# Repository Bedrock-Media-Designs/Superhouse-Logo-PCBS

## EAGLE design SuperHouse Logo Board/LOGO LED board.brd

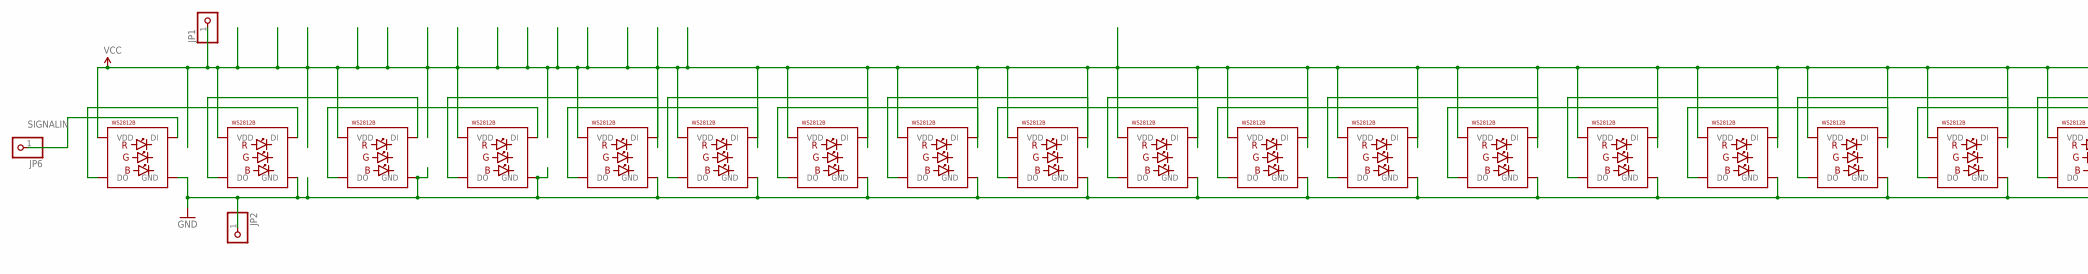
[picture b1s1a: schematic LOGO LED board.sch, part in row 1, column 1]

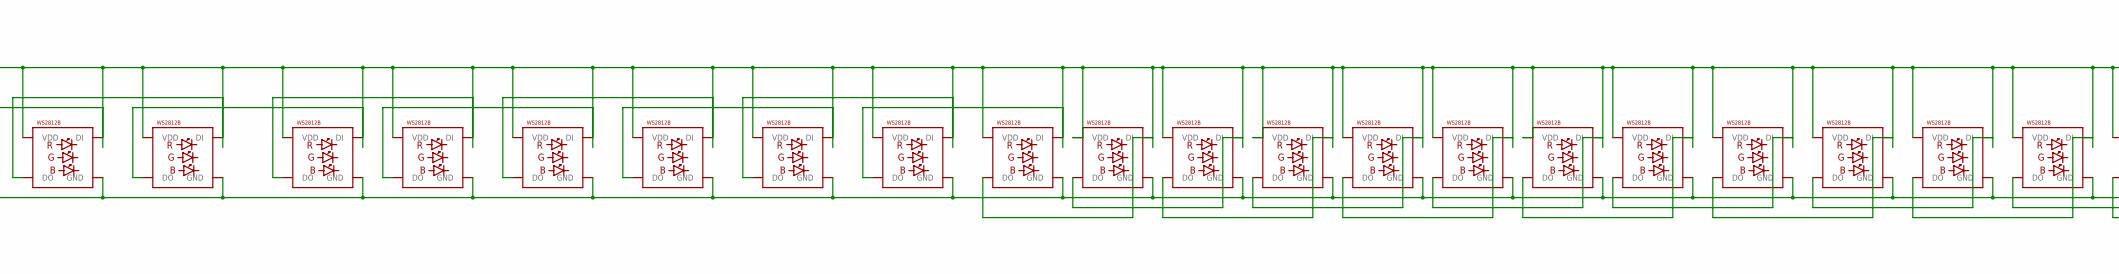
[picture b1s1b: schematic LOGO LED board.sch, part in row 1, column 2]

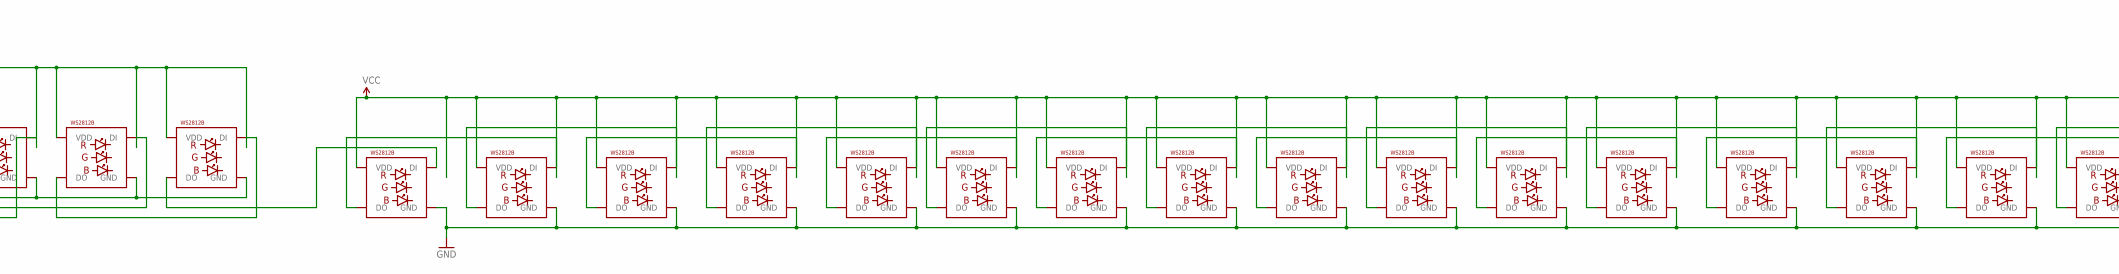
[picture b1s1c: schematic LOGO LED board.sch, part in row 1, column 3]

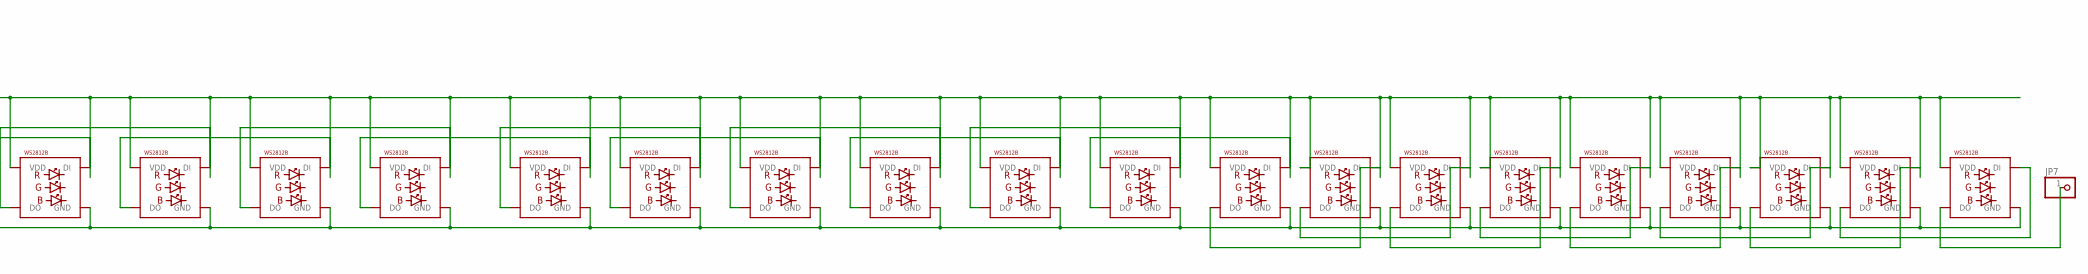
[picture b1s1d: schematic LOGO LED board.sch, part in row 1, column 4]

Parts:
JP1, JP2, JP6, JP7: PINHD-1X1; 1X01
LED1, LED2, LED3, LED4, LED5, LED6, LED7, LED8, LED9, LED10, LED11, LED12, LED13, LED14, LED15, LED16, LED17, LED18, LED19, LED20, LED21, LED22, LED23, LED24, LED25, LED26, LED27, LED28, LED29, LED30, LED31, LED32, LED33, LED34, LED35, LED36, LED37, LED38, LED39, LED40, LED41, LED42, LED43, LED44, LED45, LED46, LED47, LED48, LED49, LED50, LED51, LED52, LED53, LED54, LED55, LED56, LED57, LED58, LED59, LED60, LED61, LED62, LED63, LED64, LED65, LED66, LED67, LED68, LED69, LED70, LED71, LED72, LED73: WS2812B5050; WS2812B

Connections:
5V: JP1.1, LED1.1-VDD (VDD), LED2.1-VDD (VDD), LED3.1-VDD (VDD), LED4.1-VDD (VDD), LED5.1-VDD (VDD), LED6.1-VDD (VDD), LED7.1-VDD (VDD), LED8.1-VDD (VDD), LED9.1-VDD (VDD), LED10.1-VDD (VDD), LED11.1-VDD (VDD), LED12.1-VDD (VDD), LED13.1-VDD (VDD), LED14.1-VDD (VDD), LED15.1-VDD (VDD), LED16.1-VDD (VDD), LED17.1-VDD (VDD), LED18.1-VDD (VDD), LED19.1-VDD (VDD), LED20.1-VDD (VDD), LED21.1-VDD (VDD), LED22.1-VDD (VDD), LED23.1-VDD (VDD), LED24.1-VDD (VDD), LED25.1-VDD (VDD), LED26.1-VDD (VDD), LED27.1-VDD (VDD), LED28.1-VDD (VDD), LED29.1-VDD (VDD), LED30.1-VDD (VDD), LED31.1-VDD (VDD), LED32.1-VDD (VDD), LED33.1-VDD (VDD), LED34.1-VDD (VDD), LED35.1-VDD (VDD), LED36.1-VDD (VDD), LED37.1-VDD (VDD), LED38.1-VDD (VDD), LED39.1-VDD (VDD), LED40.1-VDD (VDD), LED41.1-VDD (VDD), LED42.1-VDD (VDD), LED43.1-VDD (VDD), LED44.1-VDD (VDD), LED45.1-VDD (VDD), LED46.1-VDD (VDD), LED47.1-VDD (VDD), LED48.1-VDD (VDD), LED49.1-VDD (VDD), LED50.1-VDD (VDD), LED51.1-VDD (VDD), LED52.1-VDD (VDD), LED53.1-VDD (VDD), LED54.1-VDD (VDD), LED55.1-VDD (VDD), LED56.1-VDD (VDD), LED57.1-VDD (VDD), LED58.1-VDD (VDD), LED59.1-VDD (VDD), LED60.1-VDD (VDD), LED61.1-VDD (VDD), LED62.1-VDD (VDD), LED63.1-VDD (VDD), LED64.1-VDD (VDD), LED65.1-VDD (VDD), LED66.1-VDD (VDD), LED67.1-VDD (VDD), LED68.1-VDD (VDD), LED69.1-VDD (VDD), LED70.1-VDD (VDD), LED71.1-VDD (VDD), LED72.1-VDD (VDD), LED73.1-VDD (VDD)
GND: JP2.1, LED1.3-GND (GND), LED2.3-GND (GND), LED3.3-GND (GND), LED4.3-GND (GND), LED5.3-GND (GND), LED6.3-GND (GND), LED7.3-GND (GND), LED8.3-GND (GND), LED9.3-GND (GND), LED10.3-GND (GND), LED11.3-GND (GND), LED12.3-GND (GND), LED13.3-GND (GND), LED14.3-GND (GND), LED15.3-GND (GND), LED16.3-GND (GND), LED17.3-GND (GND), LED18.3-GND (GND), LED19.3-GND (GND), LED20.3-GND (GND), LED21.3-GND (GND), LED22.3-GND (GND), LED23.3-GND (GND), LED24.3-GND (GND), LED25.3-GND (GND), LED26.3-GND (GND), LED27.3-GND (GND), LED28.3-GND (GND), LED29.3-GND (GND), LED30.3-GND (GND), LED31.3-GND (GND), LED32.3-GND (GND), LED33.3-GND (GND), LED34.3-GND (GND), LED35.3-GND (GND), LED36.3-GND (GND), LED37.3-GND (GND), LED38.3-GND (GND), LED39.3-GND (GND), LED40.3-GND (GND), LED41.3-GND (GND), LED42.3-GND (GND), LED43.3-GND (GND), LED44.3-GND (GND), LED45.3-GND (GND), LED46.3-GND (GND), LED47.3-GND (GND), LED48.3-GND (GND), LED49.3-GND (GND), LED50.3-GND (GND), LED51.3-GND (GND), LED52.3-GND (GND), LED53.3-GND (GND), LED54.3-GND (GND), LED55.3-GND (GND), LED56.3-GND (GND), LED57.3-GND (GND), LED58.3-GND (GND), LED59.3-GND (GND), LED60.3-GND (GND), LED61.3-GND (GND), LED62.3-GND (GND), LED63.3-GND (GND), LED64.3-GND (GND), LED65.3-GND (GND), LED66.3-GND (GND), LED67.3-GND (GND), LED68.3-GND (GND), LED69.3-GND (GND), LED70.3-GND (GND), LED71.3-GND (GND), LED72.3-GND (GND), LED73.3-GND (GND)
unnamed: LED5.2-DOUT (DO), LED6.4-DIN (DI)
unnamed: LED1.2-DOUT (DO), LED2.4-DIN (DI)
unnamed: LED2.2-DOUT (DO), LED3.4-DIN (DI)
unnamed: LED3.2-DOUT (DO), LED4.4-DIN (DI)
unnamed: LED4.2-DOUT (DO), LED5.4-DIN (DI)
unnamed: LED6.2-DOUT (DO), LED7.4-DIN (DI)
unnamed: LED7.2-DOUT (DO), LED8.4-DIN (DI)
unnamed: LED8.2-DOUT (DO), LED9.4-DIN (DI)
unnamed: LED9.2-DOUT (DO), LED10.4-DIN (DI)
unnamed: LED10.2-DOUT (DO), LED11.4-DIN (DI)
unnamed: LED11.2-DOUT (DO), LED12.4-DIN (DI)
unnamed: LED12.2-DOUT (DO), LED13.4-DIN (DI)
unnamed: LED13.2-DOUT (DO), LED14.4-DIN (DI)
unnamed: LED14.2-DOUT (DO), LED15.4-DIN (DI)
unnamed: LED15.2-DOUT (DO), LED16.4-DIN (DI)
unnamed: LED16.2-DOUT (DO), LED17.4-DIN (DI)
unnamed: LED17.2-DOUT (DO), LED18.4-DIN (DI)
unnamed: LED18.2-DOUT (DO), LED19.4-DIN (DI)
unnamed: LED19.2-DOUT (DO), LED20.4-DIN (DI)
unnamed: LED20.2-DOUT (DO), LED21.4-DIN (DI)
unnamed: LED21.2-DOUT (DO), LED22.4-DIN (DI)
unnamed: LED22.2-DOUT (DO), LED23.4-DIN (DI)
unnamed: LED23.2-DOUT (DO), LED24.4-DIN (DI)
unnamed: LED24.2-DOUT (DO), LED25.4-DIN (DI)
unnamed: LED25.2-DOUT (DO), LED26.4-DIN (DI)
unnamed: LED26.2-DOUT (DO), LED27.4-DIN (DI)
unnamed: LED27.2-DOUT (DO), LED28.4-DIN (DI)
unnamed: LED28.2-DOUT (DO), LED29.4-DIN (DI)
unnamed: LED29.2-DOUT (DO), LED30.4-DIN (DI)
unnamed: LED30.2-DOUT (DO), LED31.4-DIN (DI)
unnamed: LED31.2-DOUT (DO), LED32.4-DIN (DI)
unnamed: LED32.2-DOUT (DO), LED33.4-DIN (DI)
unnamed: LED33.2-DOUT (DO), LED34.4-DIN (DI)
unnamed: LED34.2-DOUT (DO), LED35.4-DIN (DI)
unnamed: LED35.2-DOUT (DO), LED36.4-DIN (DI)
unnamed: LED36.2-DOUT (DO), LED37.4-DIN (DI)
unnamed: LED37.2-DOUT (DO), LED38.4-DIN (DI)
unnamed: LED38.2-DOUT (DO), LED39.4-DIN (DI)
unnamed: LED40.2-DOUT (DO), LED41.4-DIN (DI)
unnamed: LED42.2-DOUT (DO), LED43.4-DIN (DI)
unnamed: LED43.2-DOUT (DO), LED44.4-DIN (DI)
unnamed: LED44.2-DOUT (DO), LED45.4-DIN (DI)
unnamed: LED45.2-DOUT (DO), LED46.4-DIN (DI)
unnamed: LED46.2-DOUT (DO), LED47.4-DIN (DI)
unnamed: LED47.2-DOUT (DO), LED48.4-DIN (DI)
unnamed: LED48.2-DOUT (DO), LED49.4-DIN (DI)
unnamed: LED49.2-DOUT (DO), LED50.4-DIN (DI)
unnamed: LED50.2-DOUT (DO), LED51.4-DIN (DI)
unnamed: LED51.2-DOUT (DO), LED52.4-DIN (DI)
unnamed: LED52.2-DOUT (DO), LED53.4-DIN (DI)
unnamed: LED53.2-DOUT (DO), LED54.4-DIN (DI)
unnamed: LED54.2-DOUT (DO), LED55.4-DIN (DI)
unnamed: LED55.2-DOUT (DO), LED56.4-DIN (DI)
unnamed: LED56.2-DOUT (DO), LED57.4-DIN (DI)
unnamed: LED57.2-DOUT (DO), LED58.4-DIN (DI)
unnamed: LED58.2-DOUT (DO), LED59.4-DIN (DI)
unnamed: LED59.2-DOUT (DO), LED60.4-DIN (DI)
unnamed: LED60.2-DOUT (DO), LED61.4-DIN (DI)
unnamed: LED61.2-DOUT (DO), LED62.4-DIN (DI)
unnamed: LED62.2-DOUT (DO), LED63.4-DIN (DI)
unnamed: LED63.2-DOUT (DO), LED64.4-DIN (DI)
unnamed: LED64.2-DOUT (DO), LED65.4-DIN (DI)
unnamed: LED41.2-DOUT (DO), LED42.4-DIN (DI)
unnamed: LED65.2-DOUT (DO), LED66.4-DIN (DI)
unnamed: LED66.2-DOUT (DO), LED67.4-DIN (DI)
unnamed: LED67.2-DOUT (DO), LED68.4-DIN (DI)
unnamed: LED68.2-DOUT (DO), LED69.4-DIN (DI)
unnamed: LED69.2-DOUT (DO), LED70.4-DIN (DI)
unnamed: LED70.2-DOUT (DO), LED71.4-DIN (DI)
unnamed: LED71.2-DOUT (DO), LED72.4-DIN (DI)
unnamed: LED72.2-DOUT (DO), LED73.4-DIN (DI)
unnamed: LED39.2-DOUT (DO), LED40.4-DIN (DI)
unnamed: JP7.1, LED73.2-DOUT (DO)
SIGNALIN: JP6.1, LED1.4-DIN (DI)

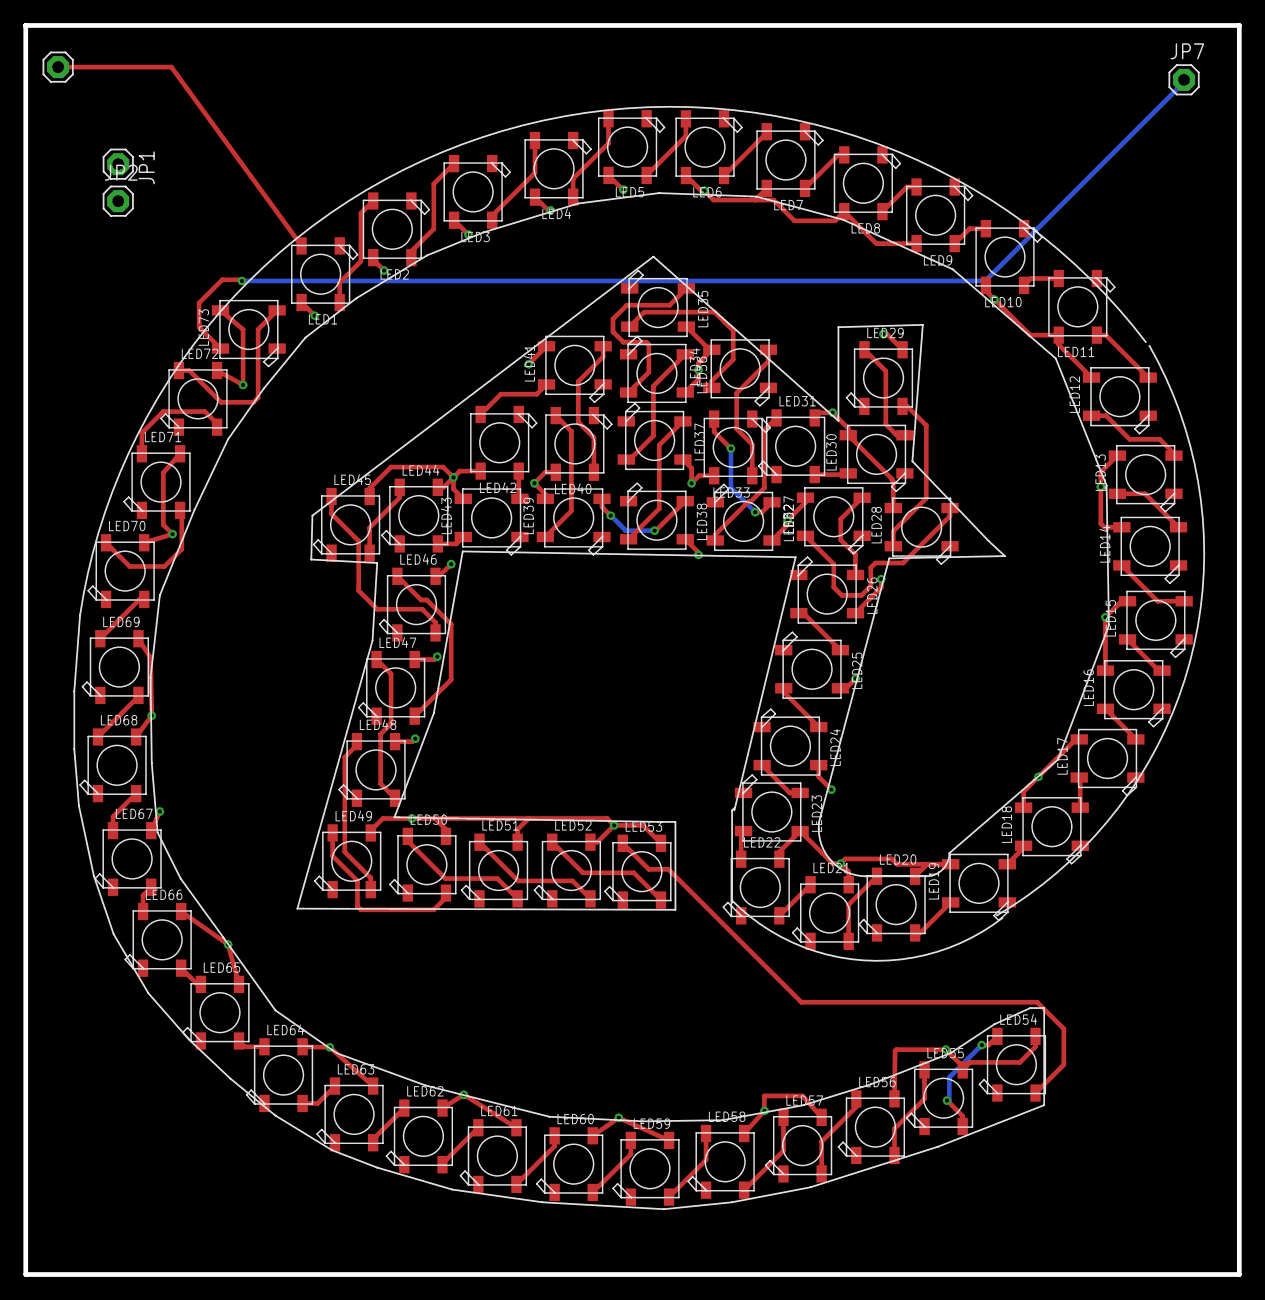
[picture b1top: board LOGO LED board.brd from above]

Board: 2 copper layers, 105.0 x 108.1 mm, 77 parts (0 on the bottom side), 76 nets.

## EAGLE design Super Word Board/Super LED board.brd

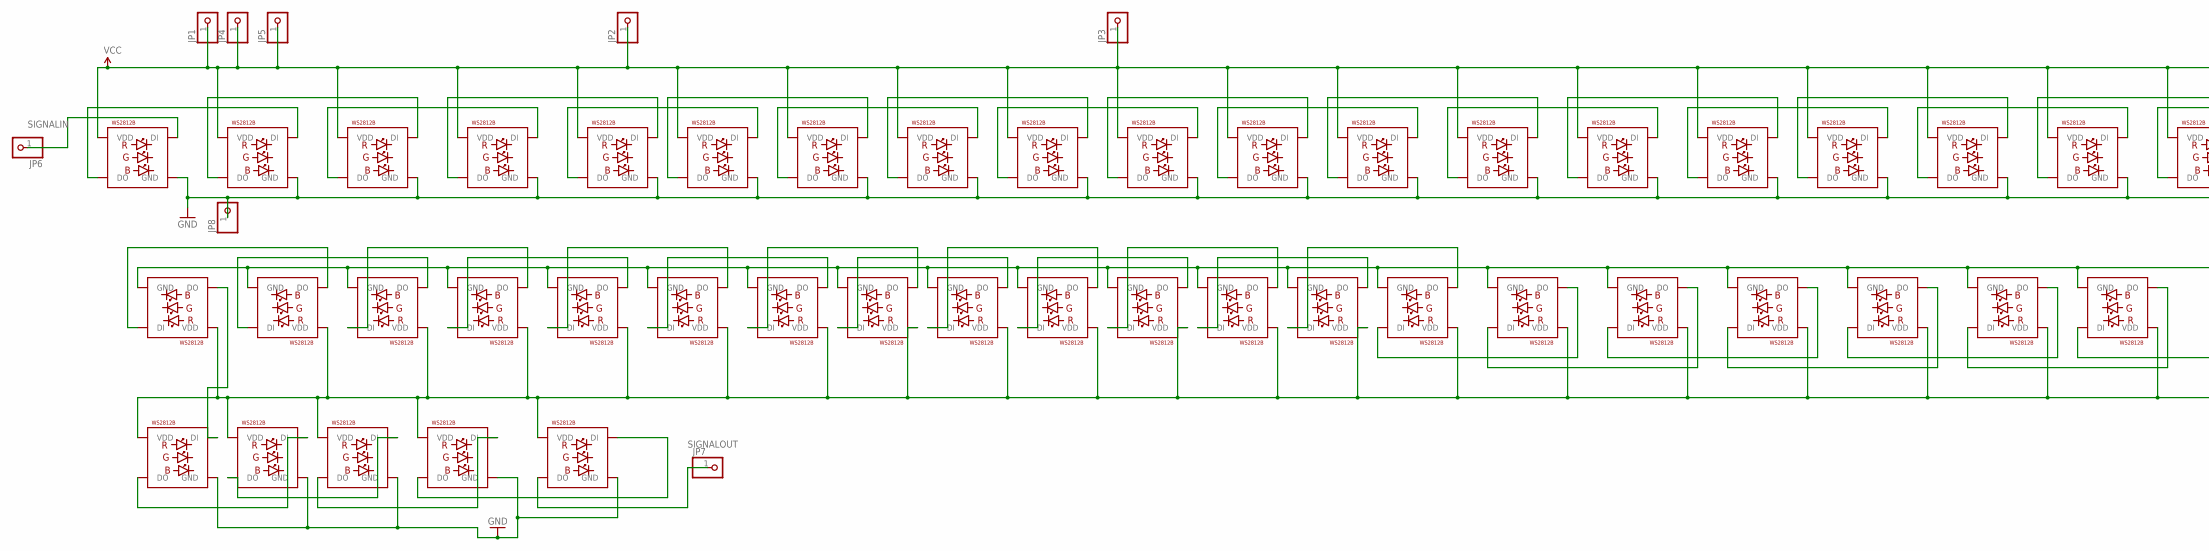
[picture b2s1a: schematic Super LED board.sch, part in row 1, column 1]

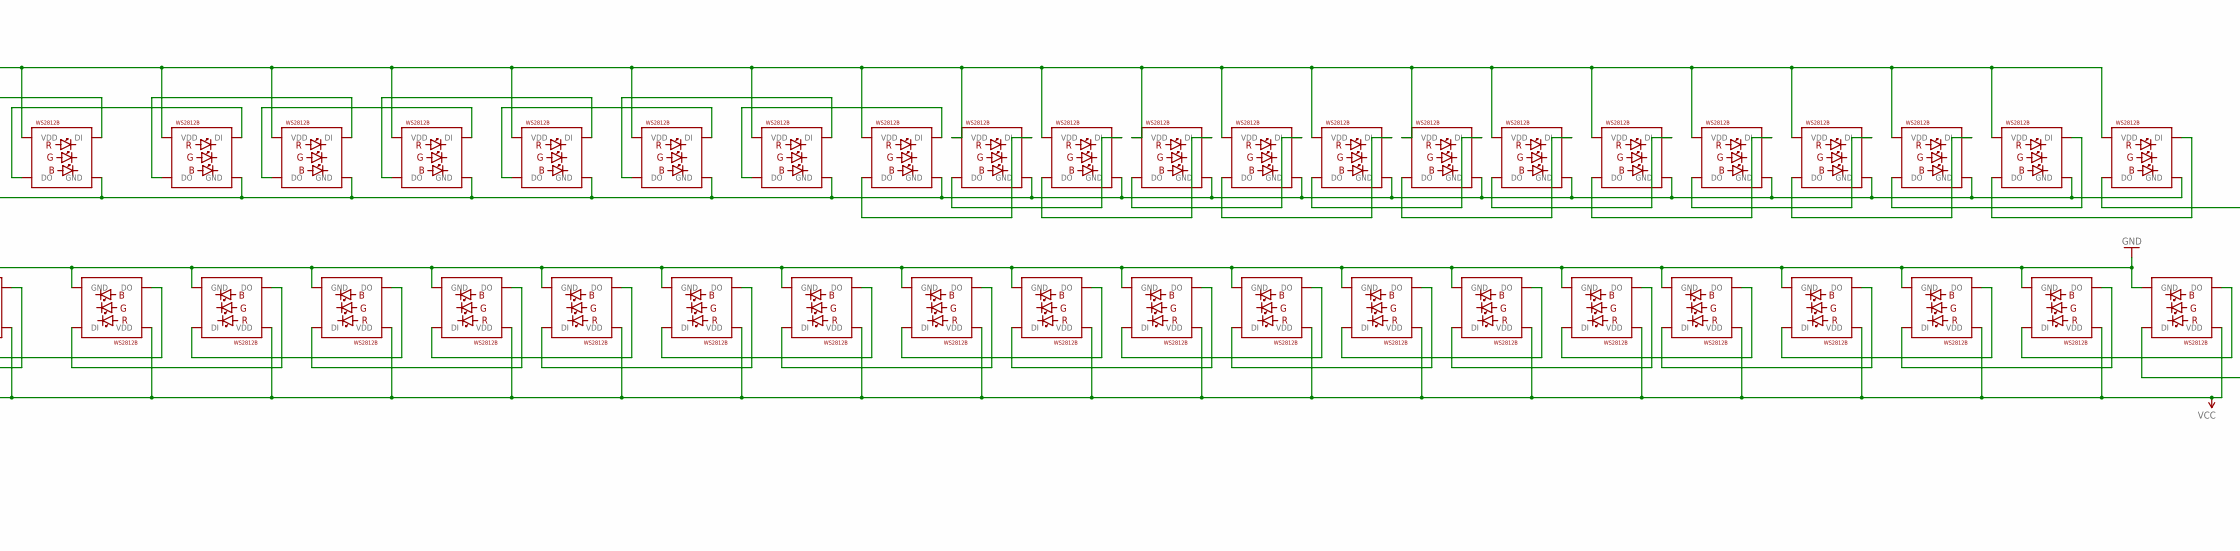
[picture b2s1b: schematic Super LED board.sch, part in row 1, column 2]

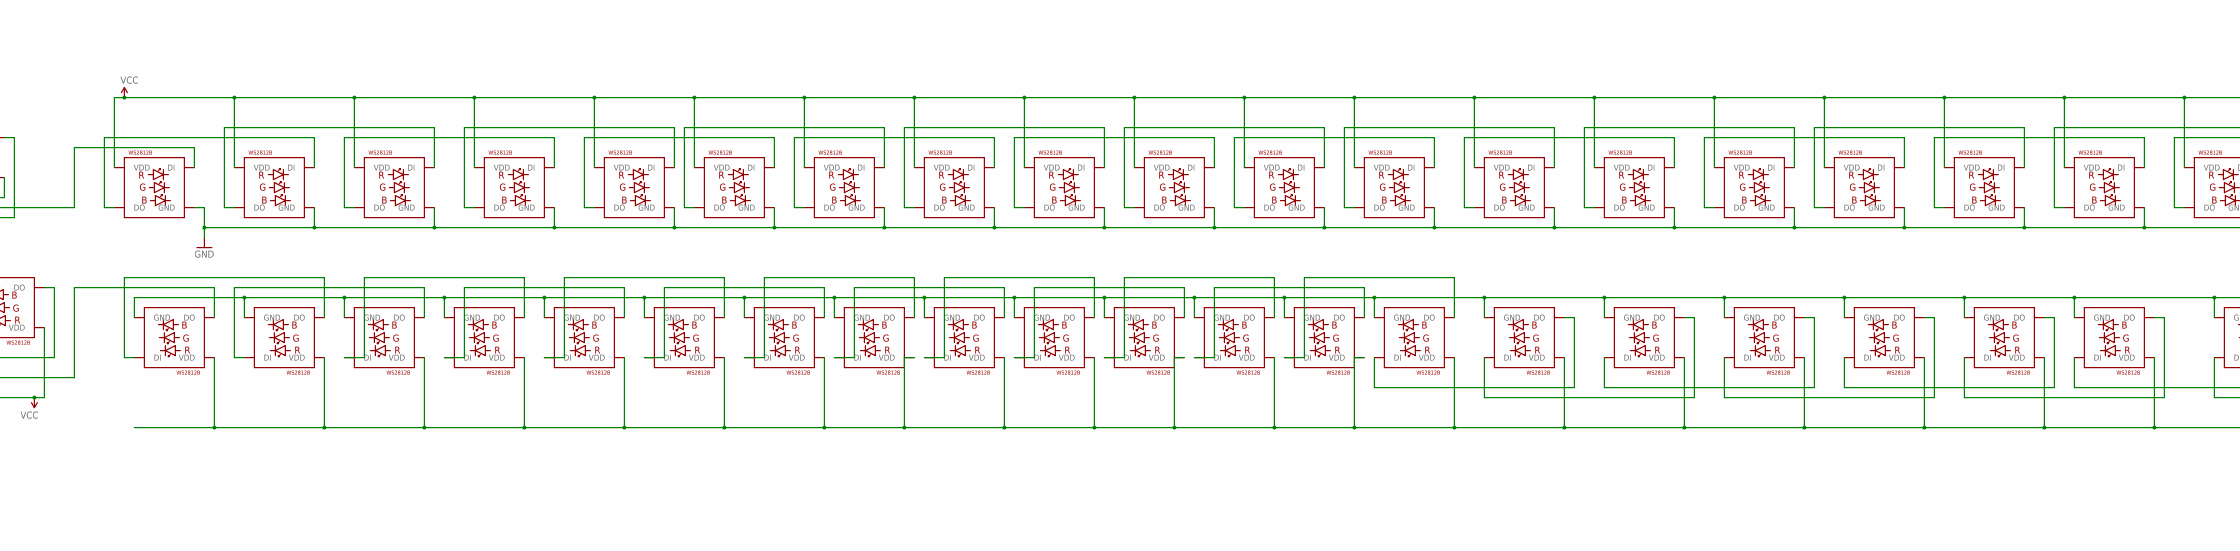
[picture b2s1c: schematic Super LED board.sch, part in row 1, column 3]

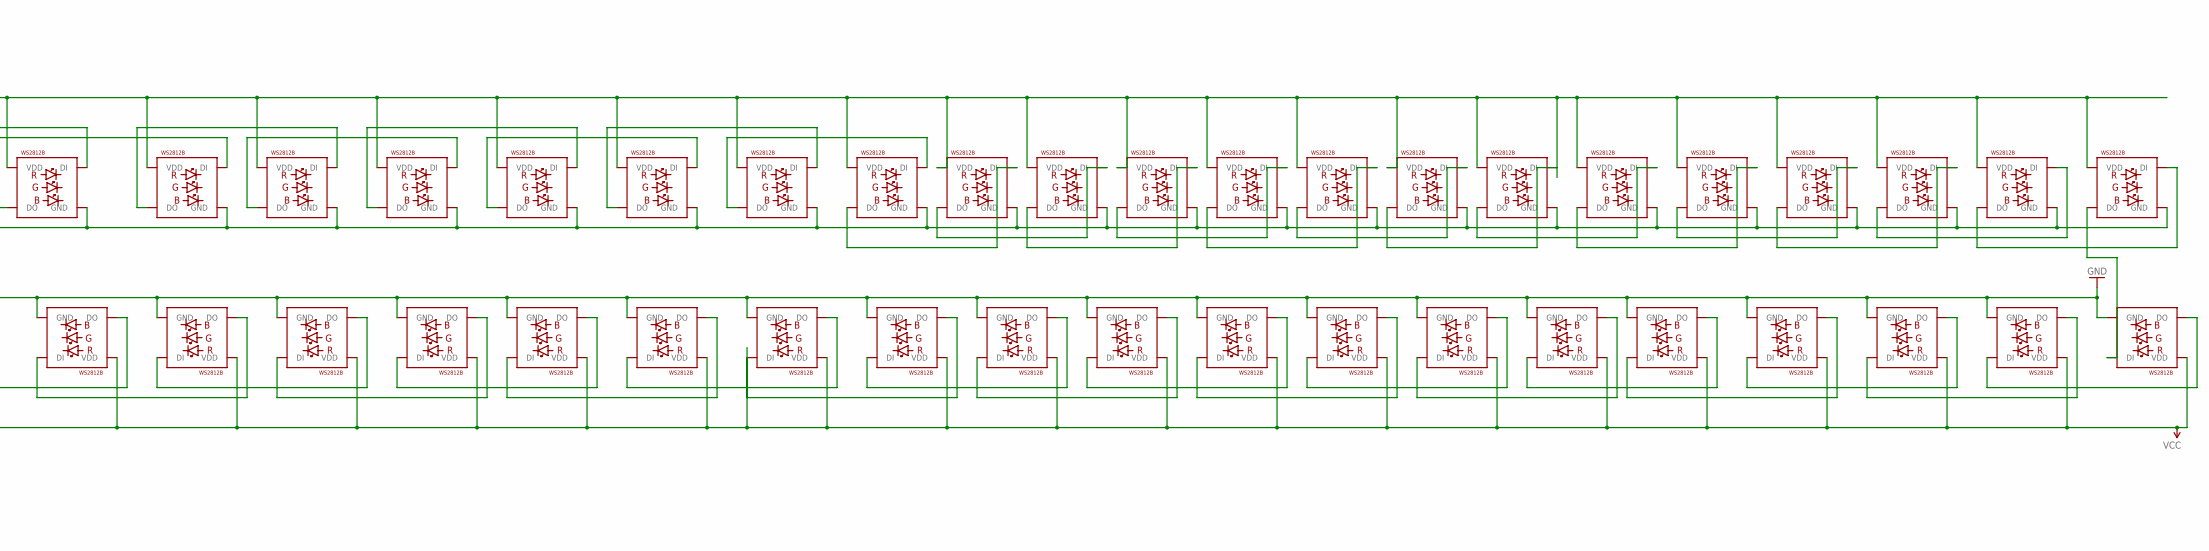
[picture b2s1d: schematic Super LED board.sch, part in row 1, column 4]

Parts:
JP1, JP2, JP3, JP4, JP5, JP6, JP7, JP8: PINHD-1X1; 1X01
LED1, LED2, LED3, LED4, LED5, LED6, LED7, LED8, LED9, LED10, LED11, LED12, LED13, LED14, LED15, LED16, LED17, LED18, LED19, LED20, LED21, LED22, LED23, LED24, LED25, LED26, LED27, LED28, LED29, LED30, LED31, LED32, LED33, LED34, LED35, LED36, LED37, LED38, LED39, LED40, LED41, LED42, LED43, LED44, LED45, LED46, LED47, LED48, LED49, LED50, LED51, LED52, LED53, LED54, LED55, LED56, LED57, LED58, LED59, LED60, LED61, LED62, LED63, LED64, LED65, LED66, LED67, LED68, LED69, LED70, LED71, LED72, LED73, LED74, LED75, LED76, LED77, LED78, LED79, LED80, LED81, LED82, LED83, LED84, LED85, LED86, LED87, LED88, LED89, LED90, LED91, LED92, LED93, LED94, LED95, LED96, LED97, LED98, LED99, LED100, LED101, LED102, LED103, LED104, LED105, LED106, LED107, LED108, LED109, LED110, LED111, LED112, LED113, LED114, LED115, LED116, LED117, LED118, LED119, LED120, LED121, LED122, LED123, LED124, LED125, LED126, LED127, LED128, LED129, LED130, LED131, LED132, LED133, LED134, LED135, LED136, LED137, LED138, LED139, LED140, LED141, LED142, LED143, LED144, LED145, LED146, LED147, LED148, LED149, LED150, LED151, LED152, LED153, LED154, LED155, LED156, LED157, LED158, LED159, LED160, LED161: WS2812B5050; WS2812B

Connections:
5V: JP1.1, JP2.1, JP3.1, JP4.1, JP5.1, LED1.1-VDD (VDD), LED2.1-VDD (VDD), LED3.1-VDD (VDD), LED4.1-VDD (VDD), LED5.1-VDD (VDD), LED6.1-VDD (VDD), LED7.1-VDD (VDD), LED8.1-VDD (VDD), LED9.1-VDD (VDD), LED10.1-VDD (VDD), LED11.1-VDD (VDD), LED12.1-VDD (VDD), LED13.1-VDD (VDD), LED14.1-VDD (VDD), LED15.1-VDD (VDD), LED16.1-VDD (VDD), LED17.1-VDD (VDD), LED18.1-VDD (VDD), LED19.1-VDD (VDD), LED20.1-VDD (VDD), LED21.1-VDD (VDD), LED22.1-VDD (VDD), LED23.1-VDD (VDD), LED24.1-VDD (VDD), LED25.1-VDD (VDD), LED26.1-VDD (VDD), LED27.1-VDD (VDD), LED28.1-VDD (VDD), LED29.1-VDD (VDD), LED30.1-VDD (VDD), LED31.1-VDD (VDD), LED32.1-VDD (VDD), LED33.1-VDD (VDD), LED34.1-VDD (VDD), LED35.1-VDD (VDD), LED36.1-VDD (VDD), LED37.1-VDD (VDD), LED38.1-VDD (VDD), LED39.1-VDD (VDD), LED40.1-VDD (VDD), LED41.1-VDD (VDD), LED42.1-VDD (VDD), LED43.1-VDD (VDD), LED44.1-VDD (VDD), LED45.1-VDD (VDD), LED46.1-VDD (VDD), LED47.1-VDD (VDD), LED48.1-VDD (VDD), LED49.1-VDD (VDD), LED50.1-VDD (VDD), LED51.1-VDD (VDD), LED52.1-VDD (VDD), LED53.1-VDD (VDD), LED54.1-VDD (VDD), LED55.1-VDD (VDD), LED56.1-VDD (VDD), LED57.1-VDD (VDD), LED58.1-VDD (VDD), LED59.1-VDD (VDD), LED60.1-VDD (VDD), LED61.1-VDD (VDD), LED62.1-VDD (VDD), LED63.1-VDD (VDD), LED64.1-VDD (VDD), LED65.1-VDD (VDD), LED66.1-VDD (VDD), LED67.1-VDD (VDD), LED68.1-VDD (VDD), LED69.1-VDD (VDD), LED70.1-VDD (VDD), LED71.1-VDD (VDD), LED72.1-VDD (VDD), LED73.1-VDD (VDD), LED74.1-VDD (VDD), LED75.1-VDD (VDD), LED76.1-VDD (VDD), LED77.1-VDD (VDD), LED78.1-VDD (VDD), LED79.1-VDD (VDD), LED80.1-VDD (VDD), LED81.1-VDD (VDD), LED82.1-VDD (VDD), LED83.1-VDD (VDD), LED84.1-VDD (VDD), LED85.1-VDD (VDD), LED86.1-VDD (VDD), LED87.1-VDD (VDD), LED88.1-VDD (VDD), LED89.1-VDD (VDD), LED90.1-VDD (VDD), LED91.1-VDD (VDD), LED92.1-VDD (VDD), LED93.1-VDD (VDD), LED94.1-VDD (VDD), LED95.1-VDD (VDD), LED96.1-VDD (VDD), LED97.1-VDD (VDD), LED98.1-VDD (VDD), LED99.1-VDD (VDD), LED100.1-VDD (VDD), LED101.1-VDD (VDD), LED102.1-VDD (VDD), LED103.1-VDD (VDD), LED104.1-VDD (VDD), LED105.1-VDD (VDD), LED106.1-VDD (VDD), LED107.1-VDD (VDD), LED108.1-VDD (VDD), LED109.1-VDD (VDD), LED110.1-VDD (VDD), LED111.1-VDD (VDD), LED112.1-VDD (VDD), LED113.1-VDD (VDD), LED114.1-VDD (VDD), LED115.1-VDD (VDD), LED116.1-VDD (VDD), LED117.1-VDD (VDD), LED118.1-VDD (VDD), LED119.1-VDD (VDD), LED120.1-VDD (VDD), LED121.1-VDD (VDD), LED122.1-VDD (VDD), LED123.1-VDD (VDD), LED124.1-VDD (VDD), LED125.1-VDD (VDD), LED126.1-VDD (VDD), LED127.1-VDD (VDD), LED128.1-VDD (VDD), LED129.1-VDD (VDD), LED130.1-VDD (VDD), LED131.1-VDD (VDD), LED132.1-VDD (VDD), LED133.1-VDD (VDD), LED134.1-VDD (VDD), LED135.1-VDD (VDD), LED136.1-VDD (VDD), LED137.1-VDD (VDD), LED138.1-VDD (VDD), LED139.1-VDD (VDD), LED140.1-VDD (VDD), LED141.1-VDD (VDD), LED142.1-VDD (VDD), LED143.1-VDD (VDD), LED144.1-VDD (VDD), LED145.1-VDD (VDD), LED146.1-VDD (VDD), LED147.1-VDD (VDD), LED148.1-VDD (VDD), LED149.1-VDD (VDD), LED150.1-VDD (VDD), LED151.1-VDD (VDD), LED152.1-VDD (VDD), LED153.1-VDD (VDD), LED154.1-VDD (VDD), LED155.1-VDD (VDD), LED156.1-VDD (VDD), LED157.1-VDD (VDD), LED158.1-VDD (VDD), LED159.1-VDD (VDD), LED160.1-VDD (VDD), LED161.1-VDD (VDD)
GND: JP8.1, LED1.3-GND (GND), LED2.3-GND (GND), LED3.3-GND (GND), LED4.3-GND (GND), LED5.3-GND (GND), LED6.3-GND (GND), LED7.3-GND (GND), LED8.3-GND (GND), LED9.3-GND (GND), LED10.3-GND (GND), LED11.3-GND (GND), LED12.3-GND (GND), LED13.3-GND (GND), LED14.3-GND (GND), LED15.3-GND (GND), LED16.3-GND (GND), LED17.3-GND (GND), LED18.3-GND (GND), LED19.3-GND (GND), LED20.3-GND (GND), LED21.3-GND (GND), LED22.3-GND (GND), LED23.3-GND (GND), LED24.3-GND (GND), LED25.3-GND (GND), LED26.3-GND (GND), LED27.3-GND (GND), LED28.3-GND (GND), LED29.3-GND (GND), LED30.3-GND (GND), LED31.3-GND (GND), LED32.3-GND (GND), LED33.3-GND (GND), LED34.3-GND (GND), LED35.3-GND (GND), LED36.3-GND (GND), LED37.3-GND (GND), LED38.3-GND (GND), LED39.3-GND (GND), LED40.3-GND (GND), LED41.3-GND (GND), LED42.3-GND (GND), LED43.3-GND (GND), LED44.3-GND (GND), LED45.3-GND (GND), LED46.3-GND (GND), LED47.3-GND (GND), LED48.3-GND (GND), LED49.3-GND (GND), LED50.3-GND (GND), LED51.3-GND (GND), LED52.3-GND (GND), LED53.3-GND (GND), LED54.3-GND (GND), LED55.3-GND (GND), LED56.3-GND (GND), LED57.3-GND (GND), LED58.3-GND (GND), LED59.3-GND (GND), LED60.3-GND (GND), LED61.3-GND (GND), LED62.3-GND (GND), LED63.3-GND (GND), LED64.3-GND (GND), LED65.3-GND (GND), LED66.3-GND (GND), LED67.3-GND (GND), LED68.3-GND (GND), LED69.3-GND (GND), LED70.3-GND (GND), LED71.3-GND (GND), LED72.3-GND (GND), LED73.3-GND (GND), LED74.3-GND (GND), LED75.3-GND (GND), LED76.3-GND (GND), LED77.3-GND (GND), LED78.3-GND (GND), LED79.3-GND (GND), LED80.3-GND (GND), LED81.3-GND (GND), LED82.3-GND (GND), LED83.3-GND (GND), LED84.3-GND (GND), LED85.3-GND (GND), LED86.3-GND (GND), LED87.3-GND (GND), LED88.3-GND (GND), LED89.3-GND (GND), LED90.3-GND (GND), LED91.3-GND (GND), LED92.3-GND (GND), LED93.3-GND (GND), LED94.3-GND (GND), LED95.3-GND (GND), LED96.3-GND (GND), LED97.3-GND (GND), LED98.3-GND (GND), LED99.3-GND (GND), LED100.3-GND (GND), LED101.3-GND (GND), LED102.3-GND (GND), LED103.3-GND (GND), LED104.3-GND (GND), LED105.3-GND (GND), LED106.3-GND (GND), LED107.3-GND (GND), LED108.3-GND (GND), LED109.3-GND (GND), LED110.3-GND (GND), LED111.3-GND (GND), LED112.3-GND (GND), LED113.3-GND (GND), LED114.3-GND (GND), LED115.3-GND (GND), LED116.3-GND (GND), LED117.3-GND (GND), LED118.3-GND (GND), LED119.3-GND (GND), LED120.3-GND (GND), LED121.3-GND (GND), LED122.3-GND (GND), LED123.3-GND (GND), LED124.3-GND (GND), LED125.3-GND (GND), LED126.3-GND (GND), LED127.3-GND (GND), LED128.3-GND (GND), LED129.3-GND (GND), LED130.3-GND (GND), LED131.3-GND (GND), LED132.3-GND (GND), LED133.3-GND (GND), LED134.3-GND (GND), LED135.3-GND (GND), LED136.3-GND (GND), LED137.3-GND (GND), LED138.3-GND (GND), LED139.3-GND (GND), LED140.3-GND (GND), LED141.3-GND (GND), LED142.3-GND (GND), LED143.3-GND (GND), LED144.3-GND (GND), LED145.3-GND (GND), LED146.3-GND (GND), LED147.3-GND (GND), LED148.3-GND (GND), LED149.3-GND (GND), LED150.3-GND (GND), LED151.3-GND (GND), LED152.3-GND (GND), LED153.3-GND (GND), LED154.3-GND (GND), LED155.3-GND (GND), LED156.3-GND (GND), LED157.3-GND (GND), LED158.3-GND (GND), LED159.3-GND (GND), LED160.3-GND (GND), LED161.3-GND (GND)
unnamed: LED5.2-DOUT (DO), LED6.4-DIN (DI)
unnamed: LED1.2-DOUT (DO), LED2.4-DIN (DI)
unnamed: LED2.2-DOUT (DO), LED3.4-DIN (DI)
unnamed: LED3.2-DOUT (DO), LED4.4-DIN (DI)
unnamed: LED4.2-DOUT (DO), LED5.4-DIN (DI)
unnamed: LED6.2-DOUT (DO), LED7.4-DIN (DI)
unnamed: LED7.2-DOUT (DO), LED8.4-DIN (DI)
unnamed: LED8.2-DOUT (DO), LED9.4-DIN (DI)
unnamed: LED9.2-DOUT (DO), LED10.4-DIN (DI)
unnamed: LED10.2-DOUT (DO), LED11.4-DIN (DI)
unnamed: LED11.2-DOUT (DO), LED12.4-DIN (DI)
unnamed: LED12.2-DOUT (DO), LED13.4-DIN (DI)
unnamed: LED13.2-DOUT (DO), LED14.4-DIN (DI)
unnamed: LED14.2-DOUT (DO), LED15.4-DIN (DI)
unnamed: LED15.2-DOUT (DO), LED16.4-DIN (DI)
unnamed: LED16.2-DOUT (DO), LED17.4-DIN (DI)
unnamed: LED17.2-DOUT (DO), LED18.4-DIN (DI)
unnamed: LED18.2-DOUT (DO), LED19.4-DIN (DI)
unnamed: LED19.2-DOUT (DO), LED20.4-DIN (DI)
unnamed: LED20.2-DOUT (DO), LED21.4-DIN (DI)
unnamed: LED21.2-DOUT (DO), LED22.4-DIN (DI)
unnamed: LED22.2-DOUT (DO), LED23.4-DIN (DI)
unnamed: LED23.2-DOUT (DO), LED24.4-DIN (DI)
unnamed: LED24.2-DOUT (DO), LED25.4-DIN (DI)
unnamed: LED25.2-DOUT (DO), LED26.4-DIN (DI)
unnamed: LED26.2-DOUT (DO), LED27.4-DIN (DI)
unnamed: LED27.2-DOUT (DO), LED28.4-DIN (DI)
unnamed: LED28.2-DOUT (DO), LED29.4-DIN (DI)
unnamed: LED29.2-DOUT (DO), LED30.4-DIN (DI)
unnamed: LED30.2-DOUT (DO), LED31.4-DIN (DI)
unnamed: LED31.2-DOUT (DO), LED32.4-DIN (DI)
unnamed: LED32.2-DOUT (DO), LED33.4-DIN (DI)
unnamed: LED33.2-DOUT (DO), LED34.4-DIN (DI)
unnamed: LED34.2-DOUT (DO), LED35.4-DIN (DI)
unnamed: LED35.2-DOUT (DO), LED36.4-DIN (DI)
unnamed: LED36.2-DOUT (DO), LED37.4-DIN (DI)
unnamed: LED37.2-DOUT (DO), LED38.4-DIN (DI)
unnamed: LED38.2-DOUT (DO), LED39.4-DIN (DI)
unnamed: LED40.2-DOUT (DO), LED41.4-DIN (DI)
unnamed: LED42.2-DOUT (DO), LED43.4-DIN (DI)
unnamed: LED43.2-DOUT (DO), LED44.4-DIN (DI)
unnamed: LED44.2-DOUT (DO), LED45.4-DIN (DI)
unnamed: LED45.2-DOUT (DO), LED46.4-DIN (DI)
unnamed: LED46.2-DOUT (DO), LED47.4-DIN (DI)
unnamed: LED47.2-DOUT (DO), LED48.4-DIN (DI)
unnamed: LED48.2-DOUT (DO), LED49.4-DIN (DI)
unnamed: LED49.2-DOUT (DO), LED50.4-DIN (DI)
unnamed: LED50.2-DOUT (DO), LED51.4-DIN (DI)
unnamed: LED51.2-DOUT (DO), LED52.4-DIN (DI)
unnamed: LED52.2-DOUT (DO), LED53.4-DIN (DI)
unnamed: LED53.2-DOUT (DO), LED54.4-DIN (DI)
unnamed: LED54.2-DOUT (DO), LED55.4-DIN (DI)
unnamed: LED55.2-DOUT (DO), LED56.4-DIN (DI)
unnamed: LED56.2-DOUT (DO), LED57.4-DIN (DI)
unnamed: LED57.2-DOUT (DO), LED58.4-DIN (DI)
unnamed: LED58.2-DOUT (DO), LED59.4-DIN (DI)
unnamed: LED59.2-DOUT (DO), LED60.4-DIN (DI)
unnamed: LED60.2-DOUT (DO), LED61.4-DIN (DI)
unnamed: LED61.2-DOUT (DO), LED62.4-DIN (DI)
unnamed: LED62.2-DOUT (DO), LED63.4-DIN (DI)
unnamed: LED63.2-DOUT (DO), LED64.4-DIN (DI)
unnamed: LED64.2-DOUT (DO), LED65.4-DIN (DI)
unnamed: LED41.2-DOUT (DO), LED42.4-DIN (DI)
unnamed: LED65.2-DOUT (DO), LED66.4-DIN (DI)
unnamed: LED66.2-DOUT (DO), LED67.4-DIN (DI)
unnamed: LED67.2-DOUT (DO), LED68.4-DIN (DI)
unnamed: LED68.2-DOUT (DO), LED69.4-DIN (DI)
unnamed: LED69.2-DOUT (DO), LED70.4-DIN (DI)
unnamed: LED70.2-DOUT (DO), LED71.4-DIN (DI)
unnamed: LED71.2-DOUT (DO), LED72.4-DIN (DI)
unnamed: LED72.2-DOUT (DO), LED73.4-DIN (DI)
unnamed: LED73.2-DOUT (DO), LED74.4-DIN (DI)
unnamed: LED74.2-DOUT (DO), LED75.4-DIN (DI)
unnamed: LED75.2-DOUT (DO), LED76.4-DIN (DI)
unnamed: LED76.2-DOUT (DO), LED77.4-DIN (DI)
unnamed: LED77.2-DOUT (DO), LED78.4-DIN (DI)
unnamed: LED39.2-DOUT (DO), LED40.4-DIN (DI)
unnamed: LED79.2-DOUT (DO), LED80.4-DIN (DI)
unnamed: LED81.2-DOUT (DO), LED82.4-DIN (DI)
unnamed: LED82.2-DOUT (DO), LED83.4-DIN (DI)
unnamed: LED83.2-DOUT (DO), LED84.4-DIN (DI)
unnamed: LED84.2-DOUT (DO), LED85.4-DIN (DI)
unnamed: LED85.2-DOUT (DO), LED86.4-DIN (DI)
unnamed: LED86.2-DOUT (DO), LED87.4-DIN (DI)
unnamed: LED87.2-DOUT (DO), LED88.4-DIN (DI)
unnamed: LED88.2-DOUT (DO), LED89.4-DIN (DI)
unnamed: LED89.2-DOUT (DO), LED90.4-DIN (DI)
unnamed: LED90.2-DOUT (DO), LED91.4-DIN (DI)
unnamed: LED91.2-DOUT (DO), LED92.4-DIN (DI)
unnamed: LED92.2-DOUT (DO), LED93.4-DIN (DI)
unnamed: LED93.2-DOUT (DO), LED94.4-DIN (DI)
unnamed: LED94.2-DOUT (DO), LED95.4-DIN (DI)
unnamed: LED95.2-DOUT (DO), LED96.4-DIN (DI)
unnamed: LED96.2-DOUT (DO), LED97.4-DIN (DI)
unnamed: LED97.2-DOUT (DO), LED98.4-DIN (DI)
unnamed: LED98.2-DOUT (DO), LED99.4-DIN (DI)
unnamed: LED99.2-DOUT (DO), LED100.4-DIN (DI)
unnamed: LED100.2-DOUT (DO), LED101.4-DIN (DI)
unnamed: LED101.2-DOUT (DO), LED102.4-DIN (DI)
unnamed: LED102.2-DOUT (DO), LED103.4-DIN (DI)
unnamed: LED103.2-DOUT (DO), LED104.4-DIN (DI)
unnamed: LED80.2-DOUT (DO), LED81.4-DIN (DI)
unnamed: LED104.2-DOUT (DO), LED105.4-DIN (DI)
unnamed: LED105.2-DOUT (DO), LED106.4-DIN (DI)
unnamed: LED106.2-DOUT (DO), LED107.4-DIN (DI)
unnamed: LED107.2-DOUT (DO), LED108.4-DIN (DI)
unnamed: LED108.2-DOUT (DO), LED109.4-DIN (DI)
unnamed: LED109.2-DOUT (DO), LED110.4-DIN (DI)
unnamed: LED110.2-DOUT (DO), LED111.4-DIN (DI)
unnamed: LED111.2-DOUT (DO), LED112.4-DIN (DI)
unnamed: LED112.2-DOUT (DO), LED113.4-DIN (DI)
unnamed: LED113.2-DOUT (DO), LED114.4-DIN (DI)
unnamed: LED114.2-DOUT (DO), LED115.4-DIN (DI)
unnamed: LED115.2-DOUT (DO), LED116.4-DIN (DI)
unnamed: LED116.2-DOUT (DO), LED117.4-DIN (DI)
unnamed: LED78.2-DOUT (DO), LED79.4-DIN (DI)
unnamed: LED118.2-DOUT (DO), LED119.4-DIN (DI)
unnamed: LED120.2-DOUT (DO), LED121.4-DIN (DI)
unnamed: LED121.2-DOUT (DO), LED122.4-DIN (DI)
unnamed: LED122.2-DOUT (DO), LED123.4-DIN (DI)
unnamed: LED123.2-DOUT (DO), LED124.4-DIN (DI)
unnamed: LED124.2-DOUT (DO), LED125.4-DIN (DI)
unnamed: LED125.2-DOUT (DO), LED126.4-DIN (DI)
unnamed: LED126.2-DOUT (DO), LED127.4-DIN (DI)
unnamed: LED127.2-DOUT (DO), LED128.4-DIN (DI)
unnamed: LED128.2-DOUT (DO), LED129.4-DIN (DI)
unnamed: LED129.2-DOUT (DO), LED130.4-DIN (DI)
unnamed: LED130.2-DOUT (DO), LED131.4-DIN (DI)
unnamed: LED131.2-DOUT (DO), LED132.4-DIN (DI)
unnamed: LED132.2-DOUT (DO), LED133.4-DIN (DI)
unnamed: LED133.2-DOUT (DO), LED134.4-DIN (DI)
unnamed: LED134.2-DOUT (DO), LED135.4-DIN (DI)
unnamed: LED135.2-DOUT (DO), LED136.4-DIN (DI)
unnamed: LED136.2-DOUT (DO), LED137.4-DIN (DI)
unnamed: LED137.2-DOUT (DO), LED138.4-DIN (DI)
unnamed: LED138.2-DOUT (DO), LED139.4-DIN (DI)
unnamed: LED139.2-DOUT (DO), LED140.4-DIN (DI)
unnamed: LED140.2-DOUT (DO), LED141.4-DIN (DI)
unnamed: LED141.2-DOUT (DO), LED142.4-DIN (DI)
unnamed: LED142.2-DOUT (DO), LED143.4-DIN (DI)
unnamed: LED119.2-DOUT (DO), LED120.4-DIN (DI)
unnamed: LED143.2-DOUT (DO), LED144.4-DIN (DI)
unnamed: LED144.2-DOUT (DO), LED145.4-DIN (DI)
unnamed: LED145.2-DOUT (DO), LED146.4-DIN (DI)
unnamed: LED146.2-DOUT (DO), LED147.4-DIN (DI)
unnamed: LED147.2-DOUT (DO), LED148.4-DIN (DI)
unnamed: LED148.2-DOUT (DO), LED149.4-DIN (DI)
unnamed: LED149.2-DOUT (DO), LED150.4-DIN (DI)
unnamed: LED150.2-DOUT (DO), LED151.4-DIN (DI)
unnamed: LED151.2-DOUT (DO), LED152.4-DIN (DI)
unnamed: LED152.2-DOUT (DO), LED153.4-DIN (DI)
unnamed: LED153.2-DOUT (DO), LED154.4-DIN (DI)
unnamed: LED154.2-DOUT (DO), LED155.4-DIN (DI)
unnamed: LED155.2-DOUT (DO), LED156.4-DIN (DI)
unnamed: LED117.2-DOUT (DO), LED118.4-DIN (DI)
unnamed: LED160.2-DOUT (DO), LED161.4-DIN (DI)
unnamed: LED156.2-DOUT (DO), LED157.4-DIN (DI)
unnamed: LED157.2-DOUT (DO), LED158.4-DIN (DI)
unnamed: LED158.2-DOUT (DO), LED159.4-DIN (DI)
unnamed: LED159.2-DOUT (DO), LED160.4-DIN (DI)
SIGNALIN: JP6.1, LED1.4-DIN (DI)
SIGNALOUT: JP7.1, LED161.2-DOUT (DO)

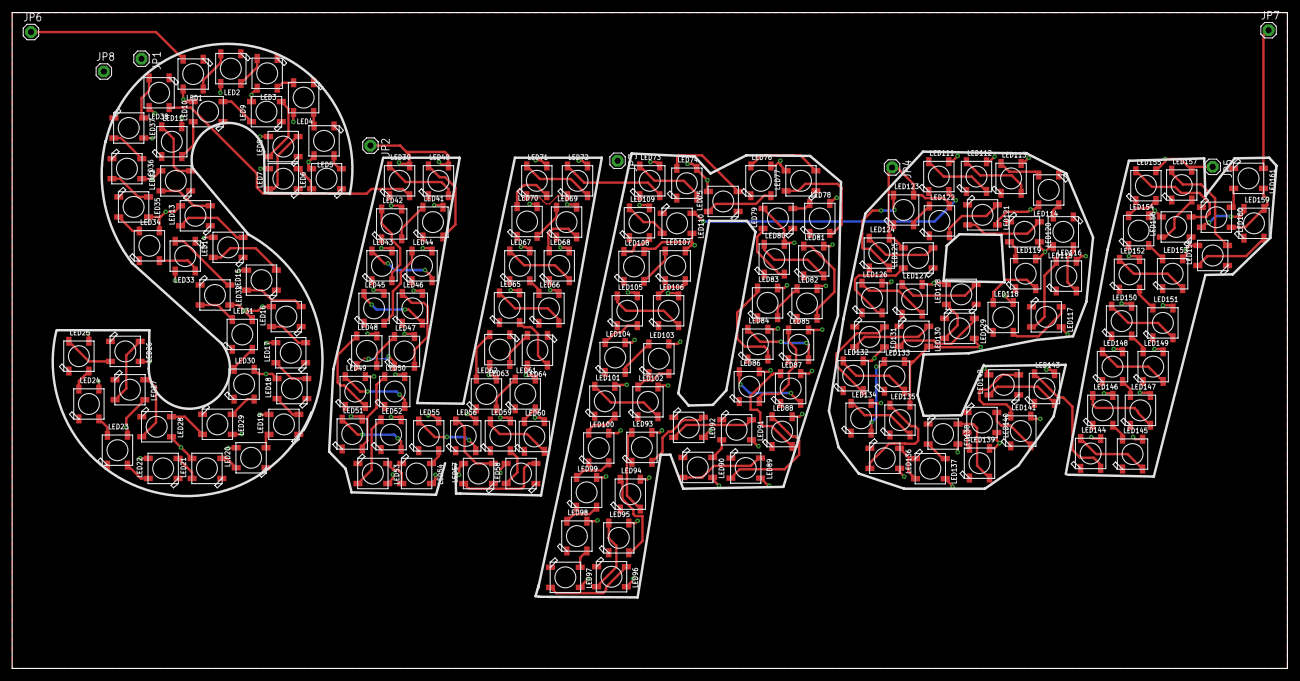
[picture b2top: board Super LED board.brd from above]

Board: 2 copper layers, 210.0 x 108.0 mm, 169 parts (0 on the bottom side), 164 nets.
